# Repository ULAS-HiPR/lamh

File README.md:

# Lámh

Lámh is the airbrake actuator node in [Ogma](https://sean-osullivan.com/projects/ogma/), the University of Limerick Aeronautics Society's modular avionics stack for high-powered rocketry.

## Role

- Drives four routed servo outputs through a PCA9685.
- Reads a physical arm input.
- Accepts time-limited actuator commands over the 500 kbit/s CAN bus.
- Enforces defined safe states when commands expire or communication is lost.

## Repository

- `hardware/` - KiCad design and manufacturing outputs.
- `firmware/` - embedded firmware, actuator probes, and tests.

## Status

Rev 1 firmware and hardware bring-up continue on [`ogma/flight-hardening`](https://github.com/ULAS-HiPR/lamh/tree/ogma/flight-hardening). Release-candidate firmware builds and software tests pass, but hardware-in-the-loop validation is still underway. Lámh is not yet flight-proven.

## Manufacturing support

Rev 1 PCB fabrication was sponsored through [EasyEDA Education](https://easyeda.com/education) and manufactured by [JLCPCB](https://jlcpcb.com/). The board was designed in KiCad and imported into EasyEDA Pro for the sponsorship and manufacturing workflow.

## More information

See the [Ogma project write-up](https://sean-osullivan.com/projects/ogma/) for the complete stack, bring-up work, and current status.

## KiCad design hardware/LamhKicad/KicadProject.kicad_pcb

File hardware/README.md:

# Hardware Notes

## PCA9685 servo outputs

The current Lamh PCB routes the PCA9685 outputs to four servo connectors:

| Connector | PCA9685 channel | Connector pin 1 | Connector pin 2 | Connector pin 3 |
| --- | ---: | --- | --- | --- |
| J4 | 0 | Signal | GND | 5v_SERVO |
| J6 | 2 | Signal | GND | 5v_SERVO |
| J2 | 4 | Signal | GND | 5v_SERVO |
| J3 | 6 | Signal | GND | 5v_SERVO |

The firmware demo currently sweeps channel 0, so plug the demo servo into J4.

## PCA9685 address

A0-A3 have pulldowns and solder jumpers to 3.3 V. For the default `0x40` address, leave those jumpers open. The firmware scans the PCA9685 hardware-address range at boot, so changed address jumpers should still work.

A4 and A5 are marked unconnected in the current PCB files. If I2C probing is unstable on a built board, strap U2 A4 and A5 low for a deterministic `0x40` address in the next hardware revision.

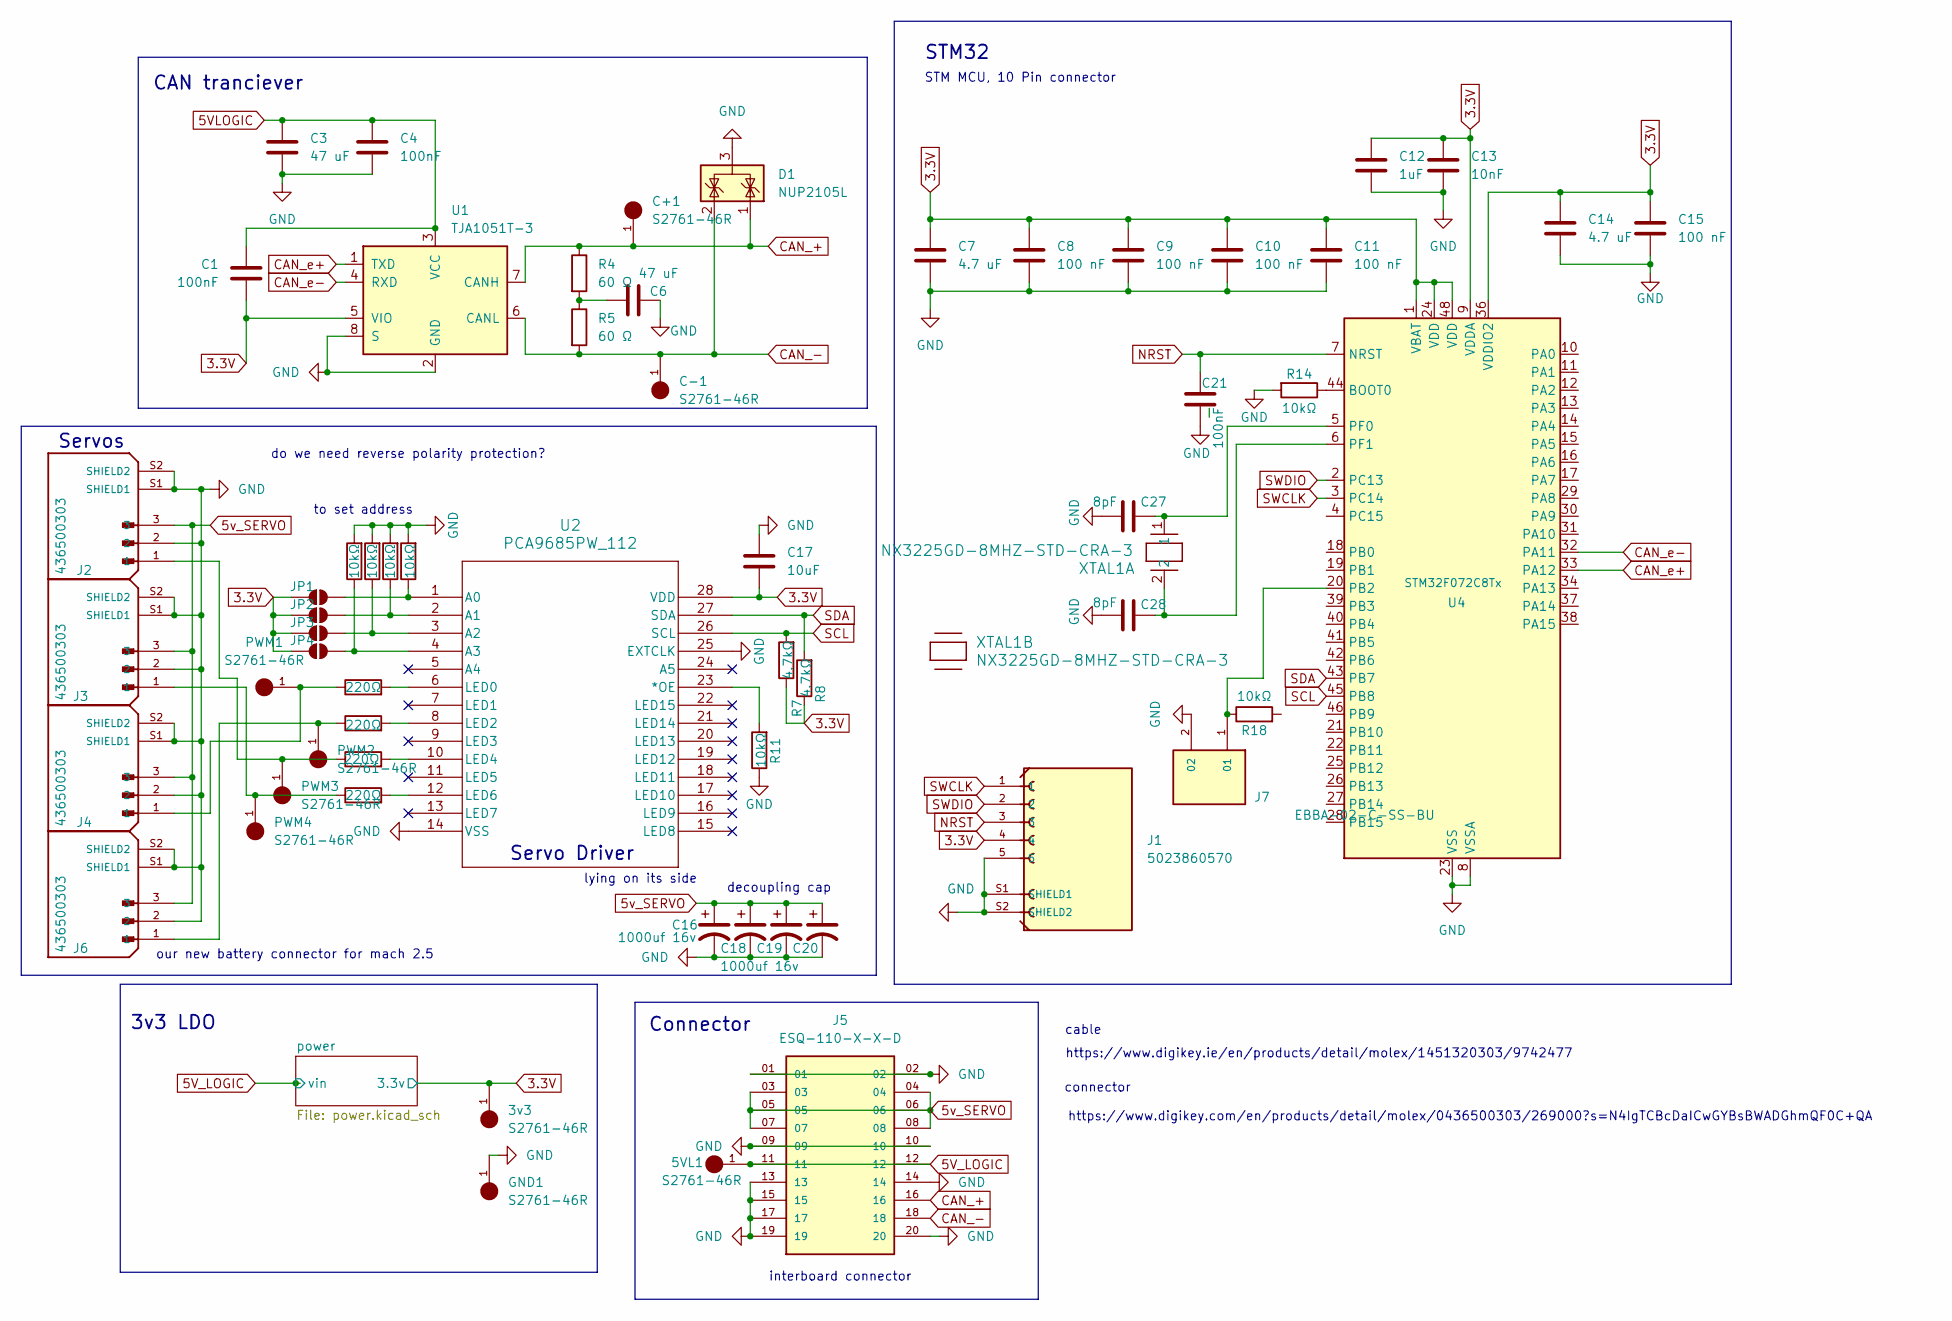
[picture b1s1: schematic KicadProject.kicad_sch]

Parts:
3v3, 5VL1: S2761-46R; HARWIN_S2761-46R; PARTREV 1
C1, C4, C21: 100nF; C_0402_1005Metric
C3, C6: 47 uF; C_0603_1608Metric
C7, C14: 4.7 uF; C_0402_1005Metric
C8, C9, C10, C11, C15: 100 nF; C_0402_1005Metric
C12: 1uF; C_0402_1005Metric
C13: 10nF; C_0603_1608Metric
C16, C18, C19, C20: 1000uf 16v; CAP_16SVPF1000MX
C17: 10uF; C_0603_1608Metric
C27, C28: 8pF; C_0402_1005Metric
C+1: S2761-46R; HARWIN_S2761-46R; PARTREV 1
C-1: S2761-46R; HARWIN_S2761-46R; PARTREV 1
D1: NUP2105L; SOT-23
GND1: S2761-46R; HARWIN_S2761-46R; PARTREV 1
J1: 5023860570; MOLEX_5023860570; PARTREV F
J2, J3, J4, J6: 436500303; MOLEX_436500303; PARTREV F3
J5: ESQ-110-X-X-D; SAMTEC_ESQ-110-14-G-D; PARTREV NA
J7: EBBA-02-C-SS-BU
JP1, JP2, JP3, JP4: SolderJumper_2_Open; SolderJumper-2_P1.3mm_Open_TrianglePad1.0x1.5mm
PWM1, PWM2, PWM3, PWM4: S2761-46R; HARWIN_S2761-46R; PARTREV 1
R1, R2, R3, R6: 220Ω; R_0402_1005Metric
R4, R5: 60 Ω; R_0402_1005Metric
R7, R8: 4.7kΩ; R_0402_1005Metric
R9, R10, R11, R12, R13, R14, R18: 10kΩ; R_0402_1005Metric
U1: TJA1051T-3; SOIC-8_3.9x4.9mm_P1.27mm
U2: PCA9685PW_112; TSSOP28_SOT361-1_NXP
U4: STM32F072C8Tx; LQFP-48_7x7mm_P0.5mm
XTAL1: NX3225GD-8MHZ-STD-CRA-3; XTAL_NX3225GD-8MHZ-STD-CRA-3_NDK

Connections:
3.3V: 3v3.1, C1.1, C7.1, C8.1, C9.1, C10.1, C11.1, C12.1, C13.1, C14.1, C15.1, C17.2, J1.4, JP1.1 (A), JP2.1 (A), JP3.1 (A), JP4.1 (A), R7.1, R8.1, U1.5 (VIO), U2.28 (VDD), U4.1 (VBAT), U4.9 (VDDA), U4.24 (VDD), U4.36 (VDDIO2), U4.48 (VDD); also elsewhere on the board
5VLOGIC: C1.2, C3.1, C4.1, U1.3 (VCC)
5V_LOGIC: 5VL1.1, J5.11, J5.12; also elsewhere on the board
5v_SERVO: C16.1, C18.1, C19.1, C20.1, J2.3, J3.3, J4.3, J5.03, J5.04, J5.05, J5.06, J5.07, J5.08, J6.3
CAN_+: C+1.1, D1.1 (K), J5.16, R4.1, U1.7 (CANH); also elsewhere on the board
CAN_-: C-1.1, D1.2 (K), J5.18, R5.2, U1.6 (CANL); also elsewhere on the board
CAN_e+: U1.1 (TXD), U4.33 (PA12)
CAN_e-: U1.4 (RXD), U4.32 (PA11)
GND: C3.2, C4.2, C6.2, C7.2, C8.2, C9.2, C10.2, C11.2, C12.2, C13.2, C14.2, C15.2, C16.2, C17.1, C18.2, C19.2, C20.2, C21.2, C27.1, C28.2, D1.3 (A), GND1.1, J1.5, J1.S1 (SHIELD1), J1.S2 (SHIELD2), J2.2, J2.S1 (SHIELD1), J2.S2 (SHIELD2), J3.2, J3.S1 (SHIELD1), J3.S2 (SHIELD2), J4.2, J4.S1 (SHIELD1), J4.S2 (SHIELD2), J5.01, J5.02, J5.09, J5.10, J5.13, J5.14, J5.15, J5.17, J5.19, J5.20, J6.2, J6.S1 (SHIELD1), J6.S2 (SHIELD2), J7.2, R9.2, R10.2, R11.1, R12.2, R13.2, R14.2, U1.2 (GND), U1.8 (S), U2.14 (VSS), U2.25 (EXTCLK), U4.8 (VSSA), U4.23 (VSS), U4.35 (VSS), U4.47 (VSS); also elsewhere on the board
NRST: C21.1, J1.3, U4.7 (NRST)
unnamed: C6.1, R4.2, R5.1
unnamed: J2.1, PWM3.1, R3.1
unnamed: J3.1, PWM4.1, R6.1
unnamed: J4.1, PWM1.1, R1.1
unnamed: J6.1, PWM2.1, R2.1
unnamed: J7.1, R18.1, U4.20 (PB2)
unnamed: JP1.2 (B), R9.1, U2.1 (A0)
unnamed: JP2.2 (B), R10.1, U2.2 (A1)
unnamed: JP3.2 (B), R12.1, U2.3 (A2)
unnamed: JP4.2 (B), R13.1, U2.4 (A3)
unnamed: R11.2, U2.23 (*OE)
unnamed: R1.2, U2.6 (LED0)
unnamed: R2.2, U2.8 (LED2)
unnamed: R3.2, U2.10 (LED4)
unnamed: R6.2, U2.12 (LED6)
unnamed: R14.1, U4.44 (BOOT0)
unnamed: C27.2, U4.5 (PF0), XTAL1.1
unnamed: C28.1, U4.6 (PF1), XTAL1.2
SCL: R7.2, U2.26 (SCL), U4.45 (PB8)
SDA: R8.2, U2.27 (SDA), U4.43 (PB7)
SWCLK: J1.1, U4.3 (PC14)
SWDIO: J1.2, U4.2 (PC13)

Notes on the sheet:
Servo Driver
Servos
interboard connector
cable
3v3 LDO
CAN tranciever
STM32
decoupling cap
our new battery connector for mach 2.5
https://www.digikey.com/en/products/detail/molex/0436500303/269000?s=N4IgTCBcDaICwGYBsBWADGhmQF0C+QA
https://www.digikey.ie/en/products/detail/molex/1451320303/9742477
connector
Connector
lying on its side
to set address
do we need reverse polarity protection?
STM MCU, 10 Pin connector

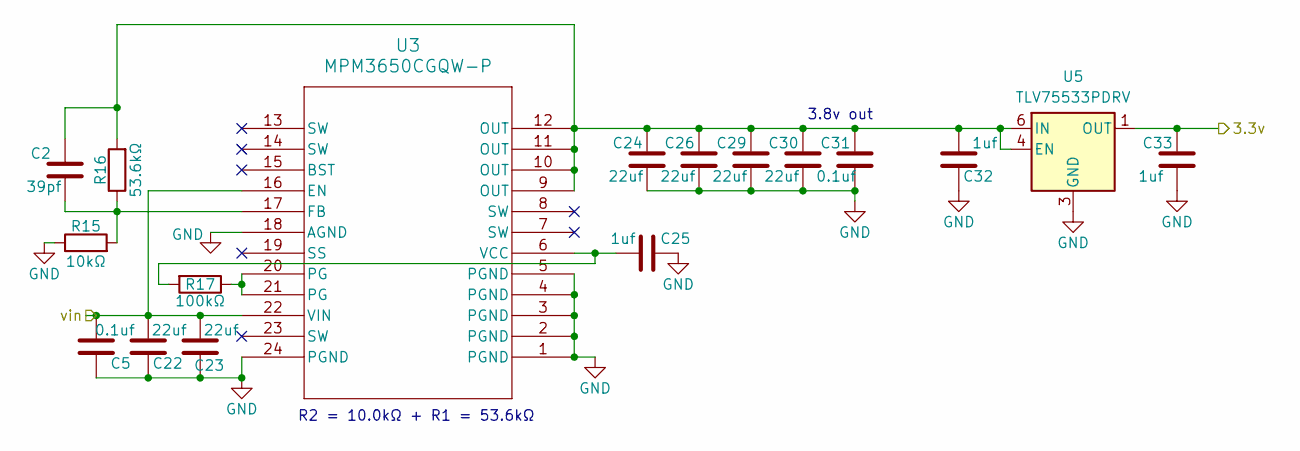
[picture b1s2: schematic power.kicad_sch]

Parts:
C2: 39pf; C_0402_1005Metric
C5, C31: 0.1uf; C_0402_1005Metric
C22, C23, C24, C26, C29, C30: 22uf; C_0603_1608Metric
C25, C32, C33: 1uf; C_0402_1005Metric
R15: 10kΩ; R_0402_1005Metric
R16: 53.6kΩ; R_0402_1005Metric
R17: 100kΩ; R_0402_1005Metric
U3: MPM3650CGQW-P; QFN-24_MPM3650_MNP
U5: TLV75533PDRV; WSON-6-1EP_2x2mm_P0.65mm_EP1x1.6mm

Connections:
3.3V: C33.1, U5.1 (OUT); also elsewhere on the board
5V_LOGIC: C5.2, C22.2, C23.2, U3.16 (EN), U3.22 (VIN); also elsewhere on the board
GND: C5.1, C22.1, C23.1, C24.2, C25.1, C26.2, C29.2, C30.2, C31.2, C32.1, C33.2, R15.1, U3.1 (PGND), U3.2 (PGND), U3.3 (PGND), U3.4 (PGND), U3.5 (PGND), U3.18 (AGND), U3.24 (PGND), U5.3 (GND), U5.7 (GND); also elsewhere on the board
unnamed: R17.1, U3.20 (PG), U3.21 (PG)
unnamed: C2.2, R15.2, R16.1, U3.17 (FB)
unnamed: C25.2, R17.2, U3.6 (VCC)
unnamed: C2.1, C24.1, C26.1, C29.1, C30.1, C31.1, C32.2, R16.2, U3.9 (OUT), U3.10 (OUT), U3.11 (OUT), U3.12 (OUT), U5.4 (EN), U5.6 (IN)

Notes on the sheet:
R2 = 10.0kΩ + R1 = 53.6kΩ
3.8v out

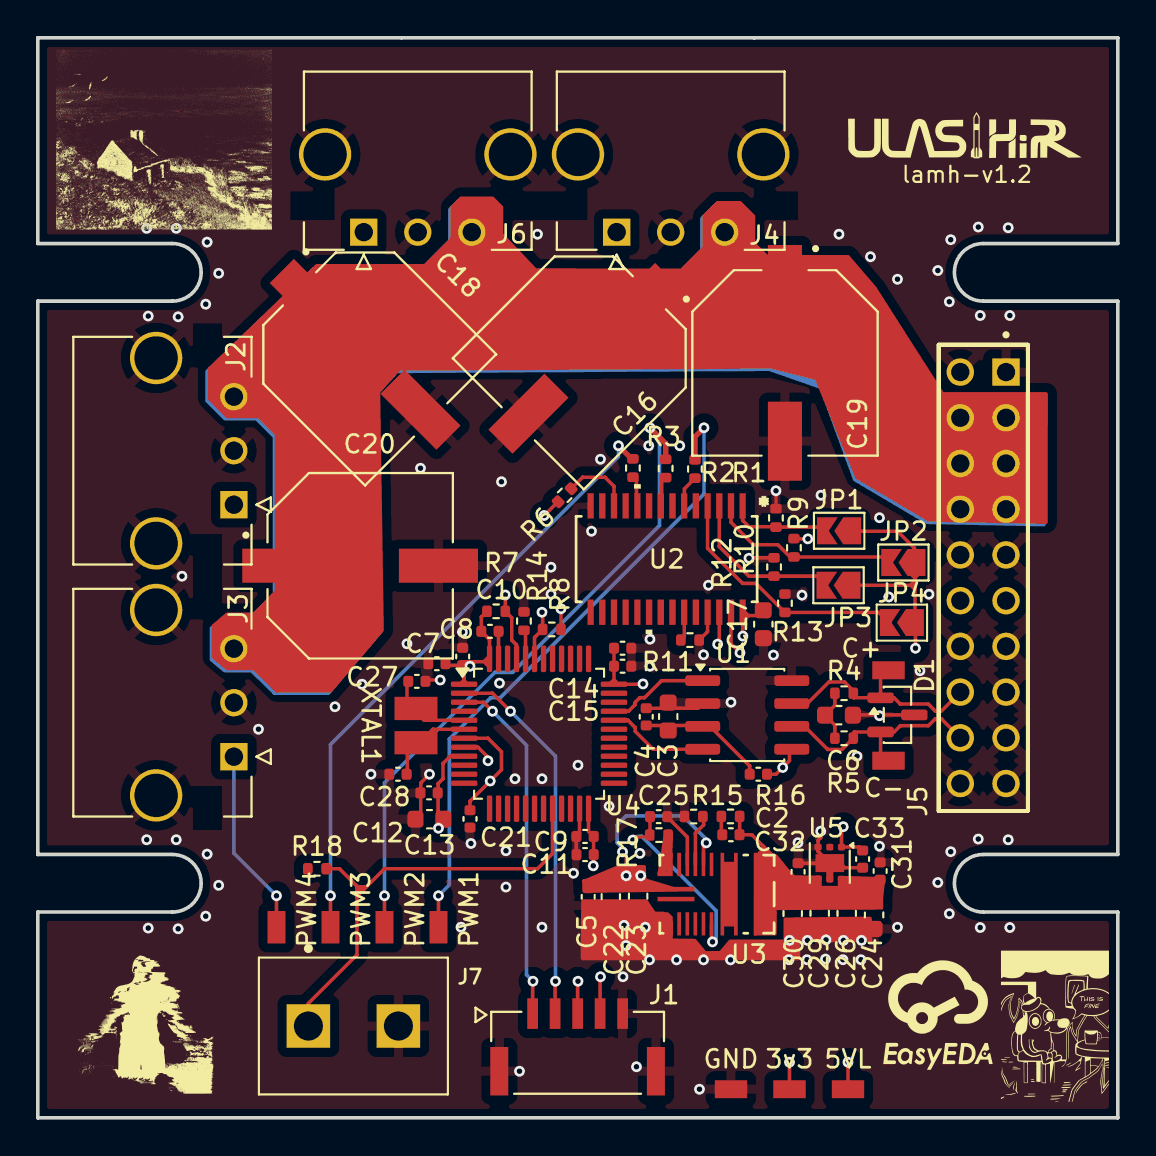
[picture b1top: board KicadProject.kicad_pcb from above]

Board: 6 copper layers, 60.0 x 60.0 mm, 78 parts (0 on the bottom side), 36 nets.

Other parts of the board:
5VL: S2761-46R; HARWIN_S2761-46R
C+: S2761-46R; HARWIN_S2761-46R
C-: S2761-46R; HARWIN_S2761-46R
GND: S2761-46R; HARWIN_S2761-46R

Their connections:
5V_LOGIC: 5VL.1; also elsewhere on the board
CAN_+: C+.1; also elsewhere on the board
CAN_-: C-.1; also elsewhere on the board
GND: GND.1; also elsewhere on the board

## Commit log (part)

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2026-01-13 code inital commit
2026-01-13 wrong workflow folder
2026-01-13 adding actions
2026-01-15 Schematic for Lamh
2026-01-15 Schematic update
2026-01-20 Some fixes to PCB editor conversion
2026-01-20 Fixed all footprints
2026-01-21 started
2026-01-21 cleaning up
2026-01-22 updates, now just need the connector
2026-01-22 progs, yes
2026-01-22 added missing 3d models
2026-01-22 outline
2026-01-22 ready to route
2026-01-22 fixed the connector
2026-01-23 minor changes
2026-01-27 added links to servo connectors
2026-01-30 thermal expansion vias
2026-02-03 3d model made
2026-02-11 mockup done, must finish routing
2026-02-20 clean asf
2026-02-23 ready for review the twost
2026-02-27 ready to go, nearly
2026-03-01 ready 2 order
2026-03-05 adding intial setup files
2026-03-05 removing DS store
2026-03-05 Fighting with submodules & PIO
2026-03-09 FC-47 Adding state machine task
2026-03-13 Adding telemetry basic task and basic logical flow to code
2026-03-13 Adding in servo to state machine and cleaning up ; & task namespace
2026-03-18 Starting to solve errors for base abstracted iteration
2026-03-23 Adding test stuff & code actully compiles now
2026-03-23 added in base logger task
2026-03-23 adding logger msg type
2026-03-23 forgot to add in logger files"
2026-03-23 attempting to add tests
2026-03-31 ready
2026-04-04 creating base tasks for acutal canards board
2026-04-04 trying to remove .vscode
2026-04-04 no vs code
2026-04-05 adding flash storage to logging
2026-04-05 adding in basic code strucutre
2026-04-05 adding in eigen submodule for canards maths
2026-04-20 F0 version is working, f4 lost cause for now
2026-04-21 no logging here & updating pins
2026-04-23 bugfixes
2026-04-29 Servo test
2026-04-30 progress on the servo front
2026-04-30 fixed file leak
2026-04-30 servo lives
2026-05-07 removing vscode files
2026-05-07 addressed most of the comments i think
2026-05-17 adding back f4 support
2026-05-17 basic logic redone once again
2026-05-17 upadting cicd
2026-05-17 I cant spell
2026-05-18 feat(SIL): linux stubs for no HW testing
2026-05-26 FreeRTOS working on f4 - ready for f0 testing
2026-05-26 making f0 compatible too
2026-05-27 Made tests for canadards controller & updated CI
2026-05-27 removing eigen
2026-05-27 fixing ci issues
2026-05-27 fixing file name
2026-06-17 feat: added active pin and logic for airbrakes activation
2026-06-22 fix: stripping back to isolate CAN
2026-06-23 feat: airbrake code implemented & and other stuff idk
2026-06-24 fix: adding rocket cd
2026-06-25 Add input pin probe firmware
2026-06-26 final airbrake loop
2026-06-29 FINAL COMMIT I HOPE
